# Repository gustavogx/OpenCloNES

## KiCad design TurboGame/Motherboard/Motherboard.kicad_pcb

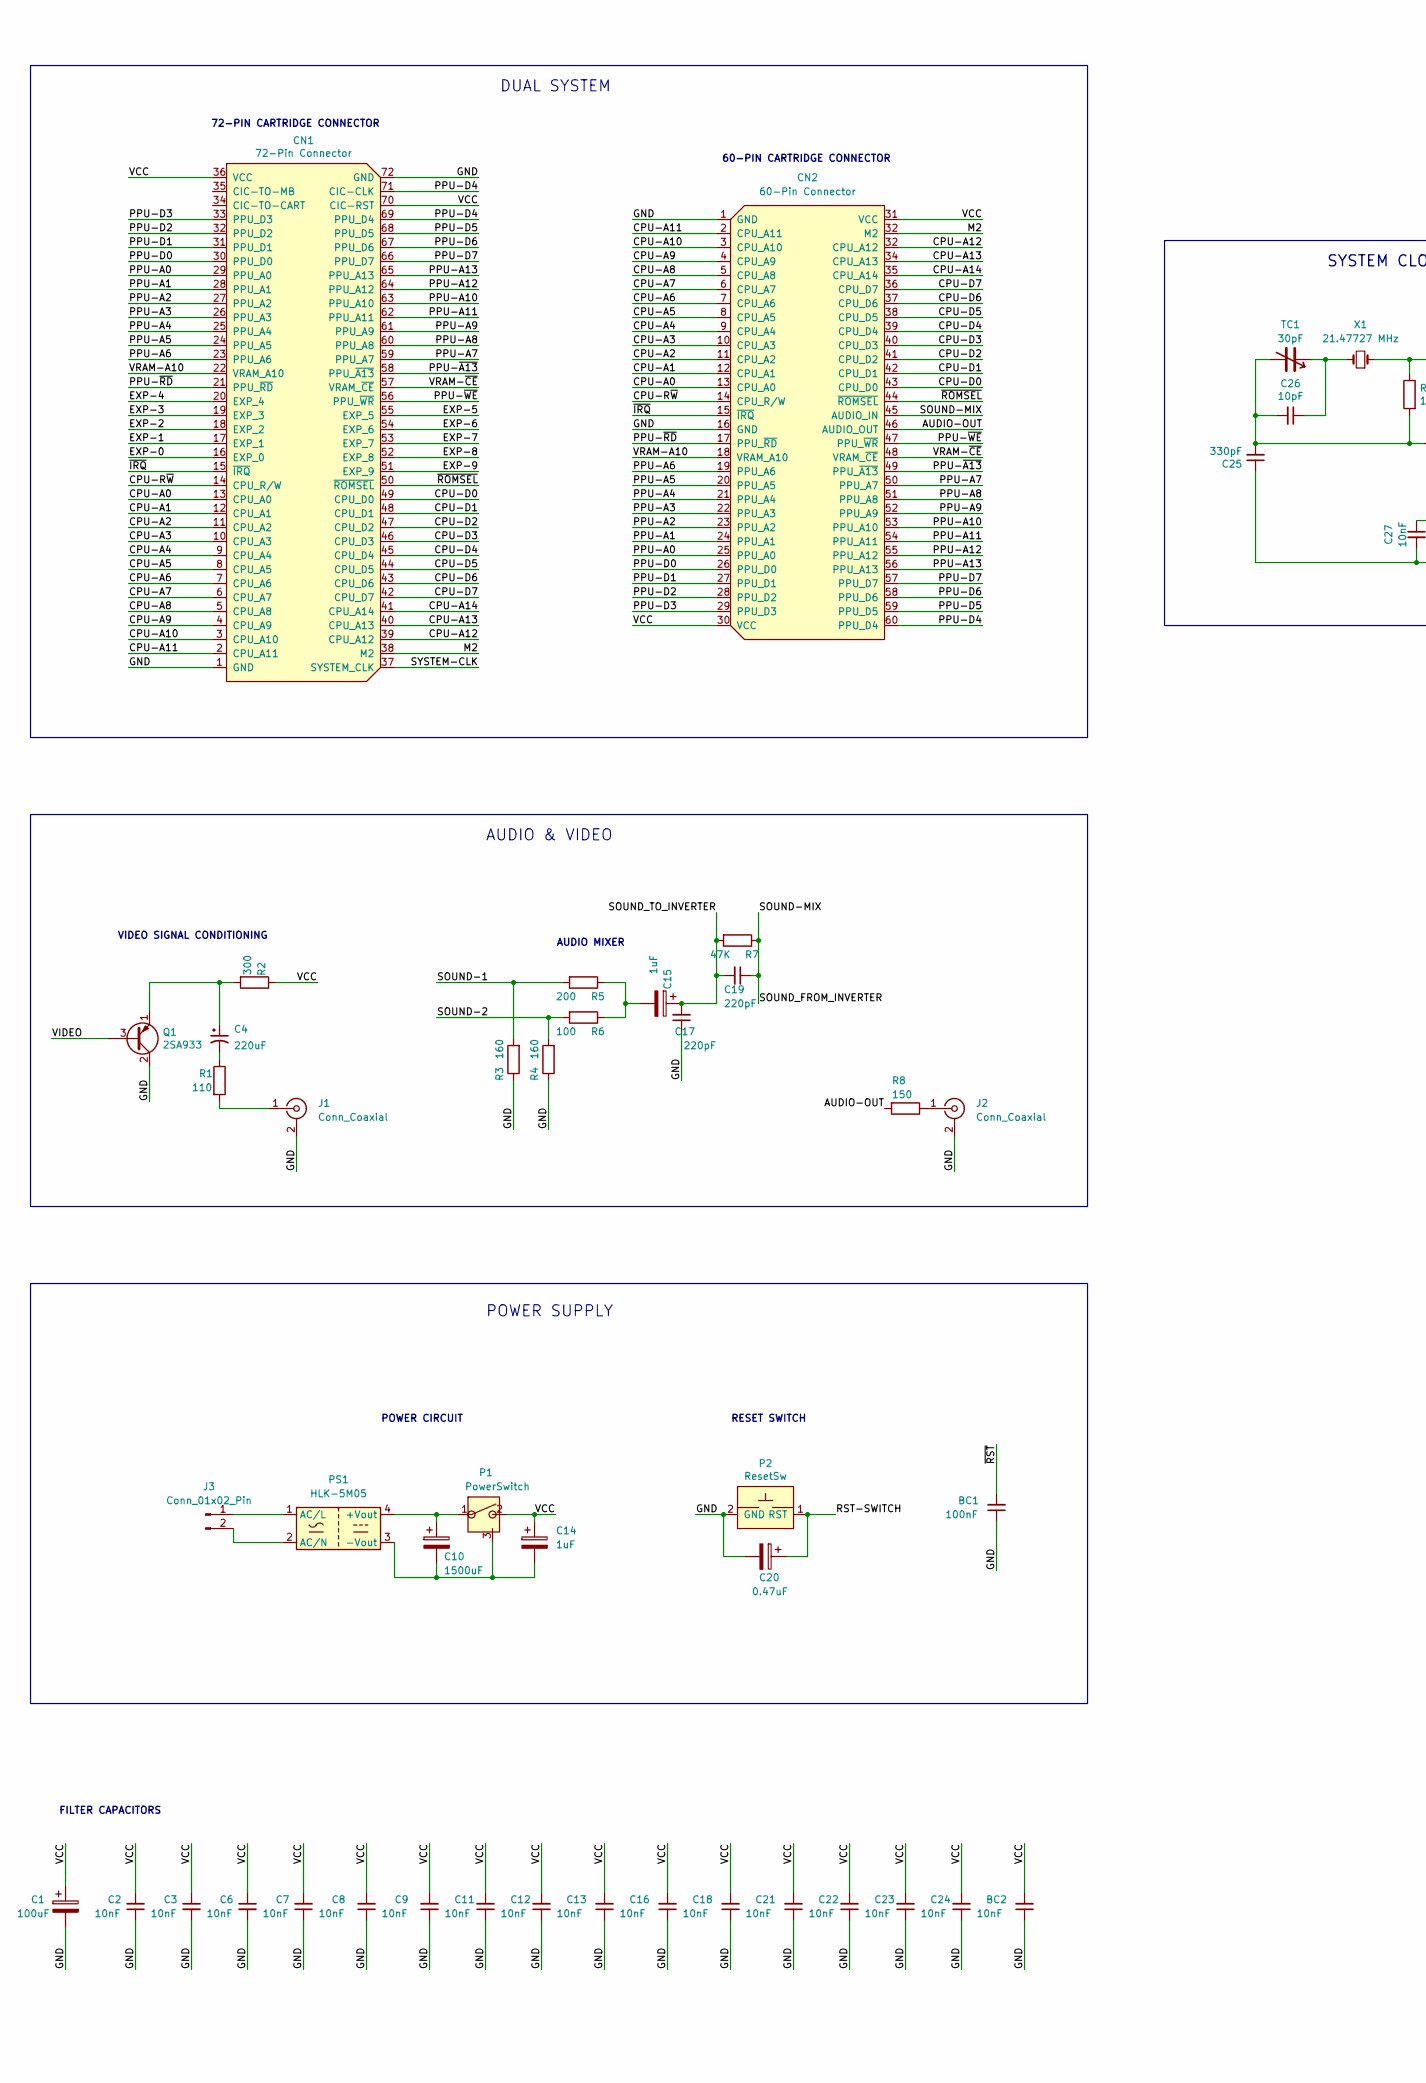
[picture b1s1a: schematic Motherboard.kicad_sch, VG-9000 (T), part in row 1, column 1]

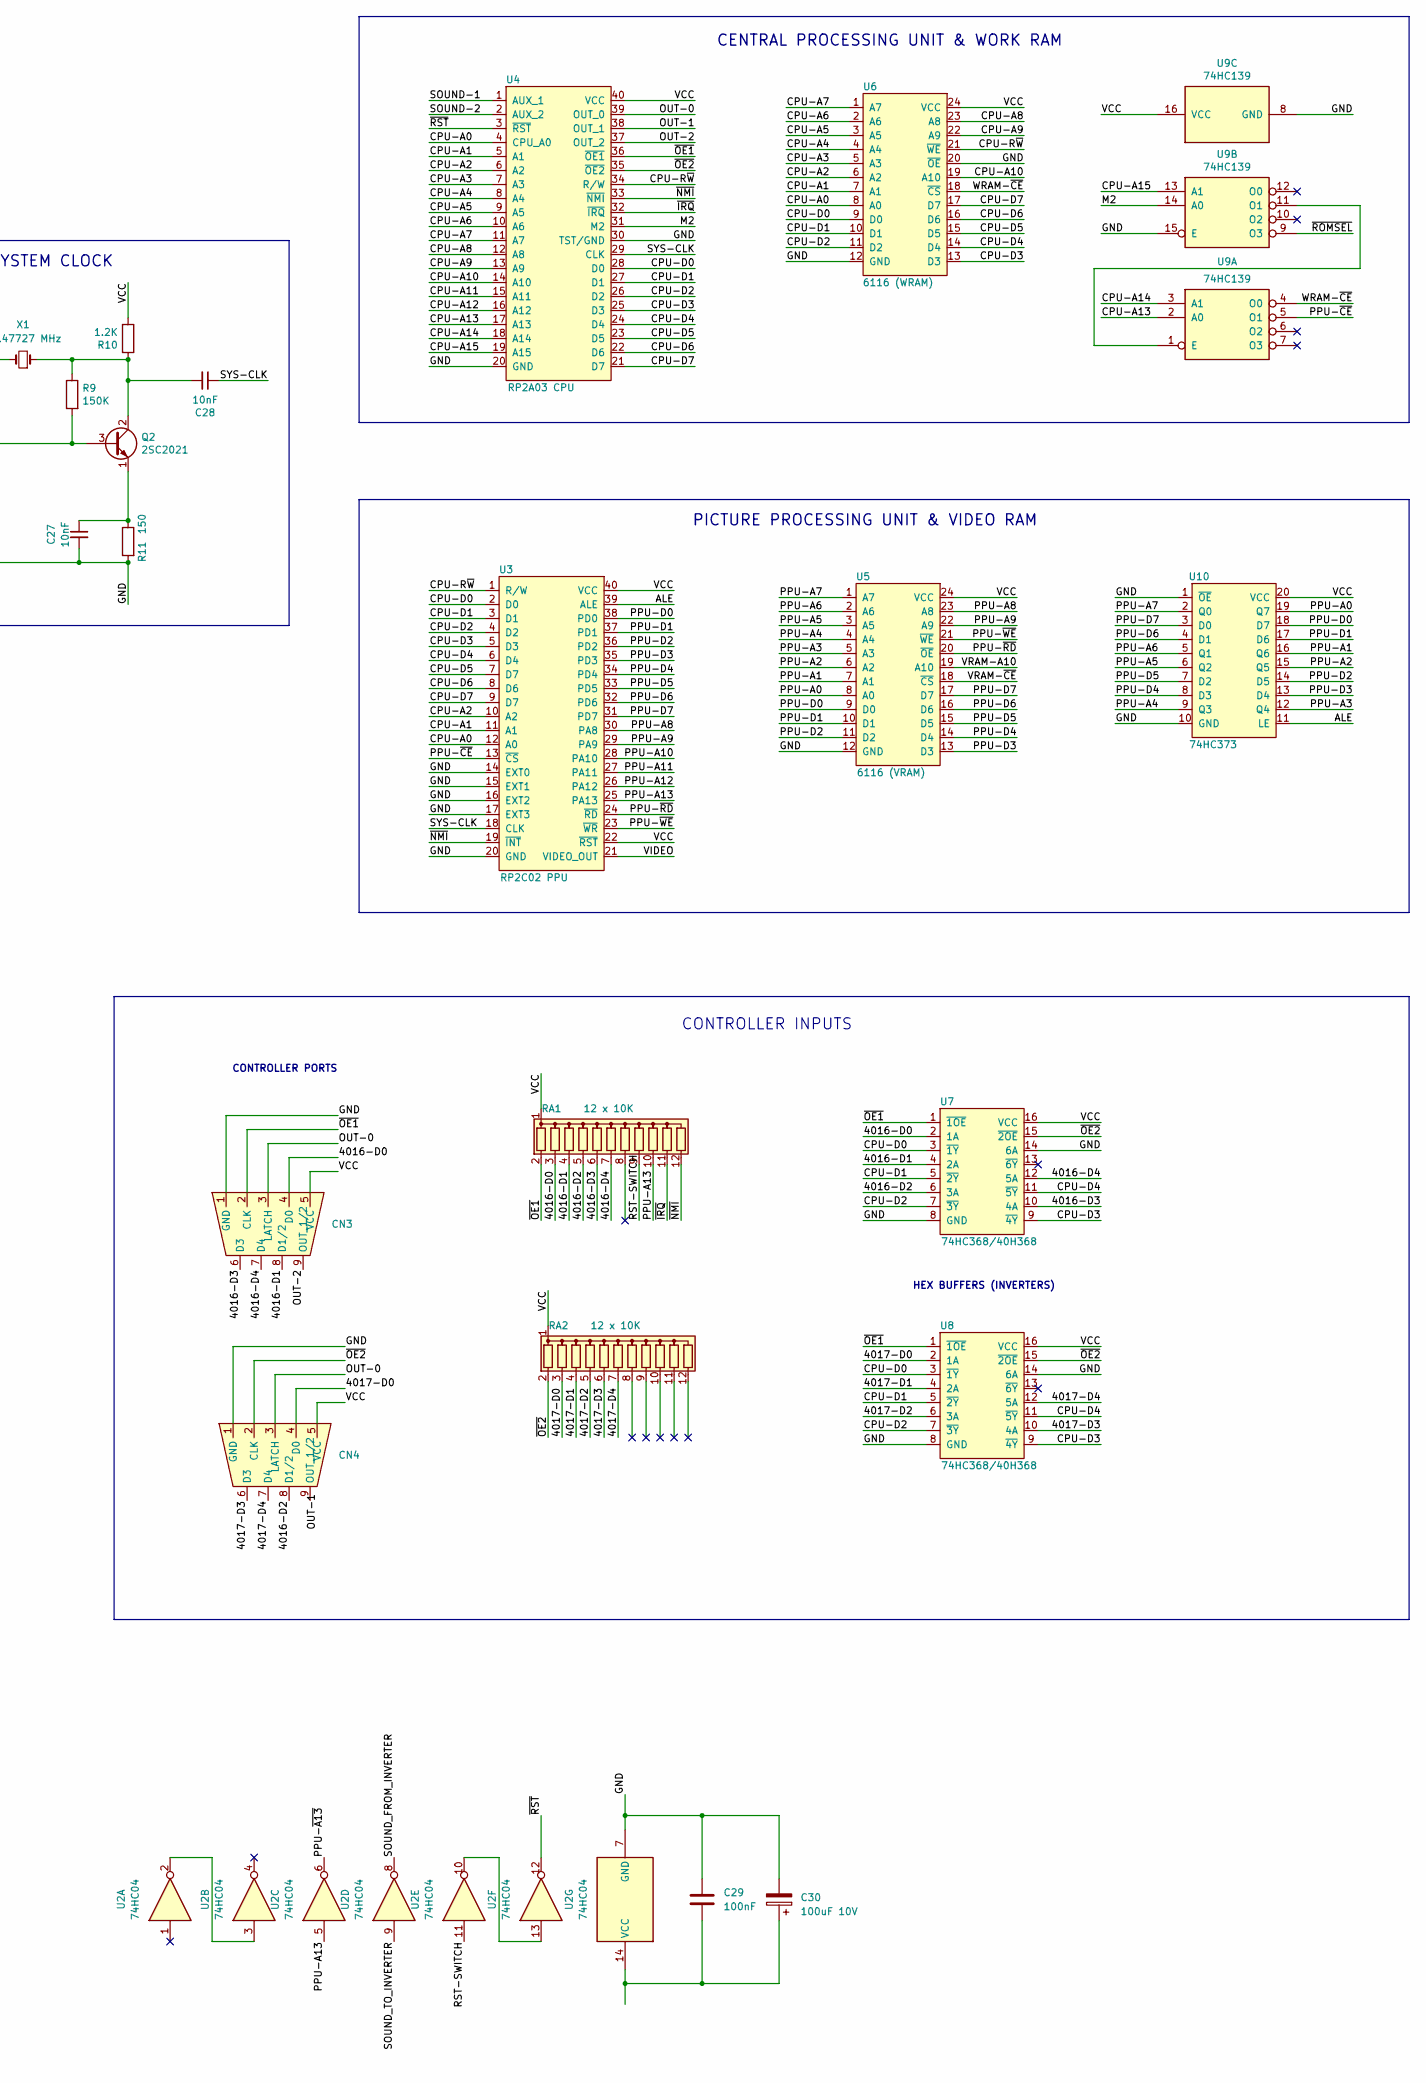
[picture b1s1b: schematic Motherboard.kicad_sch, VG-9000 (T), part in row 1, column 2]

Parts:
BC1: 100nF; C_Disc_D6.0mm_W2.5mm_P5.00mm
BC2: 10nF; C_Disc_D6.0mm_W2.5mm_P5.00mm
C1: 100uF; CP_Radial_D5.0mm_P2.00mm
C2, C3, C6, C7, C11, C12, C22, C23, C24: 10nF; C_Disc_D5.0mm_W2.5mm_P5.00mm
C4: 220uF; C_Disc_D5.0mm_W2.5mm_P5.00mm
C8: 10nF; C_Disc_D6.0mm_W2.5mm_P5.00mm
C9, C13, C16, C18, C21, C27: 10nF; C_Disc_D3.0mm_W2.0mm_P2.50mm
C10: 1500uF; CP_Radial_D12.5mm_P5.00mm
C14: 1uF; CP_Radial_D5.0mm_P2.50mm
C15: 1uF; CP_Radial_D5.0mm_P2.00mm
C17, C19: 220pF; C_Disc_D3.0mm_W1.6mm_P2.50mm
C20: 0.47uF; CP_Radial_D5.0mm_P2.00mm
C25: 330pF; C_Disc_D3.0mm_W1.6mm_P2.50mm
C26: 10pF; C_Disc_D3.0mm_W2.0mm_P2.50mm
C28: 10nF; C_Disc_D3.0mm_W1.6mm_P2.50mm
C29: 100nF; C_Disc_D5.0mm_W2.5mm_P5.00mm
C30: 100uF 10V; C_Disc_D5.0mm_W2.5mm_P5.00mm
CN1: 72-Pin Connector; 72-pin Cart Connector
CN2: 60-Pin Connector; 60-pin Cart Connector
CN3, CN4: DSUB-9_Male_Horizontal_P2.77x2.84mm_EdgePinOffset14.56mm_Ho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
J1, J2: Conn_Coaxial; RCA Jack 90deg v1
J3: Conn_01x02_Pin; JST_EH_B2B-EH-A_1x02_P2.50mm_Vertical
P1: PowerSwitch; JST_VH_B3P-VH-B_1x03_P3.96mm_Vertical
P2: ResetSw; ResetSwitch
PS1: HLK-5M05; Converter_ACDC_HiLink_HLK-5Mxx
Q1: 2SA933; TO-126-3_Vertical
Q2: 2SC2021; TO-126-3_Vertical
R1: 110; R_Axial_DIN0207_L6.3mm_D2.5mm_P10.16mm_Horizontal
R2: 300; R_Axial_DIN0207_L6.3mm_D2.5mm_P10.16mm_Horizontal
R3, R4: 160; R_Axial_DIN0207_L6.3mm_D2.5mm_P10.16mm_Horizontal
R5: 200; R_Axial_DIN0207_L6.3mm_D2.5mm_P10.16mm_Horizontal
R6: 100; R_Axial_DIN0207_L6.3mm_D2.5mm_P10.16mm_Horizontal
R7: 47K; R_Axial_DIN0207_L6.3mm_D2.5mm_P10.16mm_Horizontal
R8, R11: 150; R_Axial_DIN0207_L6.3mm_D2.5mm_P10.16mm_Horizontal
R9: 150K; R_Axial_DIN0207_L6.3mm_D2.5mm_P10.16mm_Horizontal
R10: 1.2K; R_Axial_DIN0207_L6.3mm_D2.5mm_P10.16mm_Horizontal
RA1, RA2: 12 x 10K; R_Array_SIP12
TC1: 30pF; Potentiometer_ACP_CA9-V10_Vertical
U2: 74HC04; DIP-14_W7.62mm_Socket
U3: RP2C02 PPU; DIP-40_W15.24mm
U4: RP2A03 CPU; DIP-40_W15.24mm
U5: 6116 (VRAM); DIP-24_W15.24mm
U6: 6116 (WRAM); DIP-24_W15.24mm
U7, U8: 74HC368/40H368; DIP-16_W7.62mm
U9: 74HC139; DIP-16_W7.62mm
U10: 74HC373; DIP-20_W7.62mm
X1: 21.47727 MHz; Crystal_HC49-U_Vertical

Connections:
/4016-D0: CN3.4 (D0), RA1.3 (R2), U7.2 (1A)
/4016-D1: CN3.8 (D1/2), RA1.4 (R3), U7.4 (2A)
/4016-D2: CN4.8 (D1/2), RA1.5 (R4), U7.6 (3A)
/4016-D3: CN3.6 (D3), RA1.6 (R5), U7.10 (4A)
/4016-D4: CN3.7 (D4), RA1.7 (R6), U7.12 (5A)
/4017-D0: CN4.4 (D0), RA2.3 (R2), U8.2 (1A)
/4017-D1: RA2.4 (R3), U8.4 (2A)
/4017-D2: RA2.5 (R4), U8.6 (3A)
/4017-D3: CN4.6 (D3), RA2.6 (R5), U8.10 (4A)
/4017-D4: CN4.7 (D4), RA2.7 (R6), U8.12 (5A)
/ALE: U3.39 (ALE), U10.11 (LE)
/AUDIO-OUT: CN2.46 (AUDIO_OUT), R8.2
/CPU-A0: CN1.13 (CPU_A0), CN2.13 (CPU_A0), U3.12 (A0), U4.4 (CPU_A0), U6.8 (A0)
/CPU-A1: CN1.12 (CPU_A1), CN2.12 (CPU_A1), U3.11 (A1), U4.5 (A1), U6.7 (A1)
/CPU-A2: CN1.11 (CPU_A2), CN2.11 (CPU_A2), U3.10 (A2), U4.6 (A2), U6.6 (A2)
/CPU-A3: CN1.10 (CPU_A3), CN2.10 (CPU_A3), U4.7 (A3), U6.5 (A3~)
/CPU-A4: CN1.9 (CPU_A4), CN2.9 (CPU_A4), U4.8 (A4), U6.4 (A4~)
/CPU-A5: CN1.8 (CPU_A5), CN2.8 (CPU_A5), U4.9 (A5), U6.3 (A5~)
/CPU-A6: CN1.7 (CPU_A6), CN2.7 (CPU_A6), U4.10 (A6), U6.2 (A6~)
/CPU-A7: CN1.6 (CPU_A7), CN2.6 (CPU_A7), U4.11 (A7), U6.1 (A7)
/CPU-A8: CN1.5 (CPU_A8), CN2.5 (CPU_A8), U4.12 (A8), U6.23 (A8)
/CPU-A9: CN1.4 (CPU_A9), CN2.4 (CPU_A9), U4.13 (A9), U6.22 (A9)
/CPU-A10: CN1.3 (CPU_A10), CN2.3 (CPU_A10), U4.14 (A10), U6.19 (A10)
/CPU-A11: CN1.2 (CPU_A11), CN2.2 (CPU_A11), U4.15 (A11)
/CPU-A13: CN1.40 (CPU_A13), CN2.34 (CPU_A13), U4.17 (A13), U9.2 (A0)
/CPU-A14: CN1.41 (CPU_A14), CN2.35 (CPU_A14), U4.18 (A14), U9.3 (A1)
/CPU-A15: U4.19 (A15), U9.13 (A1)
/CPU-D0: CN1.49 (CPU_D0), CN2.43 (CPU_D0), U3.2 (D0), U4.28 (D0), U6.9 (D0), U7.3 (~1Y), U8.3 (~1Y)
/CPU-D1: CN1.48 (CPU_D1), CN2.42 (CPU_D1), U3.3 (D1), U4.27 (D1), U6.10 (D1), U7.5 (~2Y), U8.5 (~2Y)
/CPU-D2: CN1.47 (CPU_D2), CN2.41 (CPU_D2), U3.4 (D2), U4.26 (D2), U6.11 (D2), U7.7 (~3Y), U8.7 (~3Y)
/CPU-D3: CN1.46 (CPU_D3), CN2.40 (CPU_D3), U3.5 (D3), U4.25 (D3), U6.13 (D3), U7.9 (~4Y), U8.9 (~4Y)
/CPU-D4: CN1.45 (CPU_D4), CN2.39 (CPU_D4), U3.6 (D4), U4.24 (D4), U6.14 (D4), U7.11 (~5Y), U8.11 (~5Y)
/CPU-D5: CN1.44 (CPU_D5), CN2.38 (CPU_D5), U3.7 (D7), U4.23 (D5), U6.15 (D5)
/CPU-D6: CN1.43 (CPU_D6), CN2.37 (CPU_D6), U3.8 (D6), U4.22 (D6), U6.16 (D6)
/CPU-D7: CN1.42 (CPU_D7), CN2.36 (CPU_D7), U3.9 (D7), U4.21 (D7), U6.17 (D7)
/CPU-R~W: CN1.14 (CPU_R/W), CN2.14 (CPU_R/W), U3.1 (R/W), U4.34 (R/W), U6.21 (~WE)
/EXP-0: CN1.16 (EXP_0)
/EXP-1: CN1.17 (EXP_1)
/EXP-2: CN1.18 (EXP_2)
/EXP-3: CN1.19 (EXP_3)
/EXP-4: CN1.20 (EXP_4)
/EXP-5: CN1.55 (EXP_5)
/EXP-6: CN1.54 (EXP_6)
/EXP-7: CN1.53 (EXP_7)
/EXP-8: CN1.52 (EXP_8)
/EXP-9: CN1.51 (EXP_9)
/GND: BC1.1, BC2.1, C1.2, C2.1, C3.2, C6.2, C7.1, C8.1, C9.1, C11.1, C12.1, C13.1, C16.1, C17.1, C18.1, C20.2, C21.1, C22.1, C23.1, C24.1, C25.1, C27.2, C29.1, C30.2, CN1.1 (GND), CN1.72 (GND), CN2.1 (GND), CN2.16 (GND), CN3.1 (GND), CN4.1 (GND), J1.2 (Ext), J2.2 (Ext), P2.2 (GND), Q1.2 (C), R3.1, R4.1, R11.2, U2.7 (GND), U3.14 (EXT0), U3.15 (EXT1), U3.16 (EXT2), U3.17 (EXT3), U3.20 (GND), U4.20 (GND), U4.30 (TST/GND), U5.12 (GND~), U6.12 (GND~), U6.20 (~OE), U7.8 (GND), U7.14 (6A), U8.8 (GND), U8.14 (6A), U9.8 (GND), U9.15 (E), U10.1 (~OE), U10.10 (GND)
/OUT-0: CN3.3 (LATCH), CN4.3 (LATCH), U4.39 (OUT_0)
/OUT-1: U4.38 (OUT_1)
/OUT-2: CN3.9 (OUT_1/2), U4.37 (OUT_2)
/PPU-A0: CN1.29 (PPU_A0), CN2.25 (PPU_A0), U5.8 (A0), U10.19 (Q7)
/PPU-A1: CN1.28 (PPU_A1), CN2.24 (PPU_A1), U5.7 (A1), U10.16 (Q6)
/PPU-A2: CN1.27 (PPU_A2), CN2.23 (PPU_A2), U5.6 (A2), U10.15 (Q5)
/PPU-A3: CN1.26 (PPU_A3), CN2.22 (PPU_A3), U5.5 (A3~), U10.12 (Q4)
/PPU-A4: CN1.25 (PPU_A4), CN2.21 (PPU_A4), U5.4 (A4~), U10.9 (Q3)
/PPU-A5: CN1.24 (PPU_A5), CN2.20 (PPU_A5), U5.3 (A5~), U10.6 (Q2)
/PPU-A6: CN1.23 (PPU_A6), CN2.19 (PPU_A6), U5.2 (A6~), U10.5 (Q1)
/PPU-A7: CN1.59 (PPU_A7), CN2.50 (PPU_A7), U5.1 (A7), U10.2 (Q0)
/PPU-A8: CN1.60 (PPU_A8), CN2.51 (PPU_A8), U3.30 (PA8), U5.23 (A8)
/PPU-A9: CN1.61 (PPU_A9), CN2.52 (PPU_A9), U3.29 (PA9), U5.22 (A9)
/PPU-A10: CN1.63 (PPU_A10), CN2.53 (PPU_A10), U3.28 (PA10)
/PPU-A11: CN1.62 (PPU_A11), CN2.54 (PPU_A11), U3.27 (PA11)
/PPU-A12: CN1.64 (PPU_A12), CN2.55 (PPU_A12), U3.26 (PA12)
/PPU-A13: CN1.65 (PPU_A13), CN2.56 (PPU_A13), RA1.10 (R9), U2.5, U3.25 (PA13)
/PPU-D0: CN1.30 (PPU_D0), CN2.26 (PPU_D0), U3.38 (PD0), U5.9 (D0), U10.18 (D7)
/PPU-D1: CN1.31 (PPU_D1), CN2.27 (PPU_D1), U3.37 (PD1), U5.10 (D1), U10.17 (D6)
/PPU-D2: CN1.32 (PPU_D2), CN2.28 (PPU_D2), U3.36 (PD2), U5.11 (D2), U10.14 (D5)
/PPU-D3: CN1.33 (PPU_D3), CN2.29 (PPU_D3), U3.35 (PD3), U5.13 (D3), U10.13 (D4)
/PPU-D4: CN1.69 (PPU_D4), CN1.71 (CIC-CLK), CN2.60 (PPU_D4), U3.34 (PD4), U5.14 (D4), U10.8 (D3)
/PPU-D5: CN1.68 (PPU_D5), CN2.59 (PPU_D5), U3.33 (PD5), U5.15 (D5), U10.7 (D2)
/PPU-D6: CN1.67 (PPU_D6), CN2.58 (PPU_D6), U3.32 (PD6), U5.16 (D6), U10.4 (D1)
/PPU-D7: CN1.66 (PPU_D7), CN2.57 (PPU_D7), U3.31 (PD7), U5.17 (D7), U10.3 (D0)
/PPU-~A13: CN1.58 (PPU_~A13), CN2.49 (PPU_~A13), U2.6
/PPU-~CE: U3.13 (~CS), U9.5 (O1)
/PPU-~RD: CN1.21 (PPU_~RD), CN2.17 (PPU_~RD), U3.24 (~RD), U5.20 (~OE)
/PPU-~WE: CN1.56 (PPU_~WR), CN2.47 (PPU_~WR), U3.23 (~WR), U5.21 (~WE)
/RST-SWITCH: C20.1, P2.1 (RST), RA1.9 (R8), U2.11
/SOUND-1: R3.2, R5.2, U4.1 (AUX_1)
/SOUND-2: R4.2, R6.2, U4.2 (AUX_2)
/SOUND-MIX: C19.1, CN2.45 (AUDIO_IN), R7.1, U2.8
/SOUND_TO_INVERTER: C15.1, C17.2, C19.2, R7.2, U2.9
/SYS-CLK: C28.1, U3.18 (CLK), U4.29 (CLK)
/SYSTEM-CLK: CN1.37 (SYSTEM_CLK)
/VCC: BC2.2, C1.1, C2.2, C3.1, C6.1, C7.2, C8.2, C9.2, C11.2, C12.2, C13.2, C14.1, C16.2, C18.2, C21.2, C22.2, C23.2, C24.2, CN1.36 (VCC), CN1.70 (CIC-RST), CN2.30 (VCC), CN2.31 (VCC), CN3.5 (VCC), CN4.5 (VCC), P1.2, R2.1, R10.2, RA1.1 (common), RA2.1 (common), U3.22 (~RST), U3.40 (VCC), U4.40 (VCC), U5.24 (VCC), U6.24 (VCC), U7.16 (VCC), U8.16 (VCC), U9.16 (VCC), U10.20 (VCC)
/VIDEO: Q1.3 (B), U3.21 (VIDEO_OUT)
/VRAM-A10: CN1.22 (VRAM_A10), CN2.18 (VRAM_A10), U5.19 (A10)
/VRAM-~CE: CN1.57 (VRAM_~CE), CN2.48 (VRAM_~CE), U5.18 (~CS)
/WRAM-~CE: U6.18 (~CS), U9.4 (O0)
/~IRQ: CN1.15 (~IRQ), CN2.15 (~IRQ), RA1.11 (R10), U4.32 (~IRQ)
/~NMI: RA1.12 (R11), U3.19 (~INT), U4.33 (~NMI)
/~OE1: CN3.2 (CLK), RA1.2 (R1), U4.36 (~OE1), U7.1 (~1OE), U8.1 (~1OE)
/~OE2: CN4.2 (CLK), RA2.2 (R1), U4.35 (~OE2), U7.15 (~2OE), U8.15 (~2OE)
/~ROMSEL: CN1.50 (~ROMSEL), CN2.44 (~ROMSEL), U9.9 (O3)
/~RST: BC1.2, U2.12, U4.3 (~RST)
unnamed: C4.2, R1.1
unnamed: C15.2, R5.1, R6.1
unnamed: C26.1, TC1.1, X1.2
unnamed: J1.1 (In), R1.2
unnamed: J2.1 (In), R8.1
unnamed: J3.1, PS1.1 (AC/L)
unnamed: J3.2, PS1.2 (AC/N)
unnamed: C10.1, P1.1, PS1.4 (+Vout)
unnamed: C10.2, C14.2, P1.3, PS1.3 (-Vout)
unnamed: C4.1, Q1.1 (E), R2.2
unnamed: C25.2, C26.2, Q2.3 (B), R9.2, TC1.2
unnamed: C28.2, Q2.2 (C), R9.1, R10.1, X1.1
unnamed: C27.1, Q2.1 (E), R11.1
unnamed: U2.2, U2.3
unnamed: U2.10, U2.13
unnamed: C29.2, C30.1, U2.14 (VCC)
unnamed: U9.1 (E), U9.11 (O1)

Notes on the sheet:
CENTRAL PROCESSING UNIT & WORK RAM
AUDIO MIXER
HEX BUFFERS (INVERTERS)
72-PIN CARTRIDGE CONNECTOR
PICTURE PROCESSING UNIT & VIDEO RAM
VIDEO SIGNAL CONDITIONING
AUDIO & VIDEO
DUAL SYSTEM
POWER CIRCUIT
SYSTEM CLOCK
FILTER CAPACITORS
POWER SUPPLY
60-PIN CARTRIDGE CONNECTOR
CONTROLLER INPUTS
CONTROLLER PORTS
RESET SWITCH

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
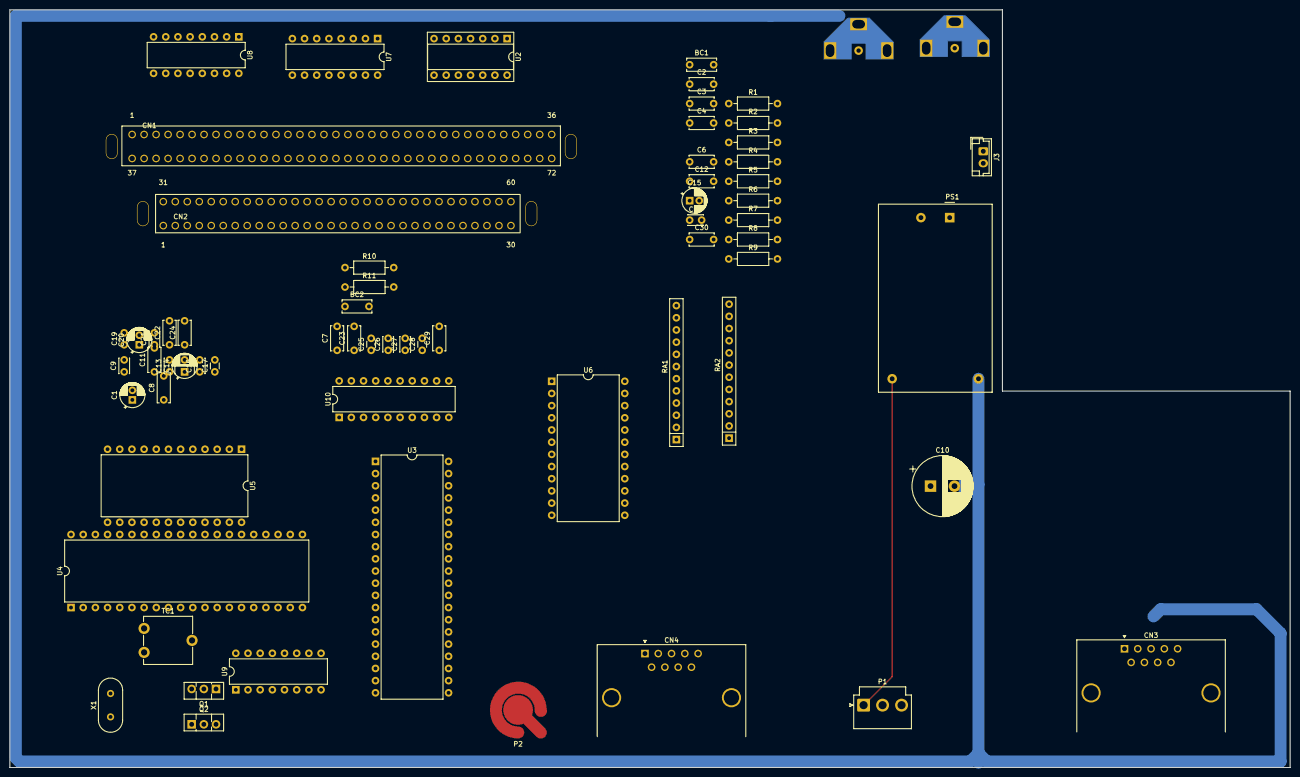
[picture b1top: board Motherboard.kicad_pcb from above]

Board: 2 copper layers, 267.0 x 158.0 mm, 67 parts (0 on the bottom side), 101 nets.
